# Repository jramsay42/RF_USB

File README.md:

# RF_USB
Simple pcb using a NRF2401 transceiver, inspired by Phil's lab

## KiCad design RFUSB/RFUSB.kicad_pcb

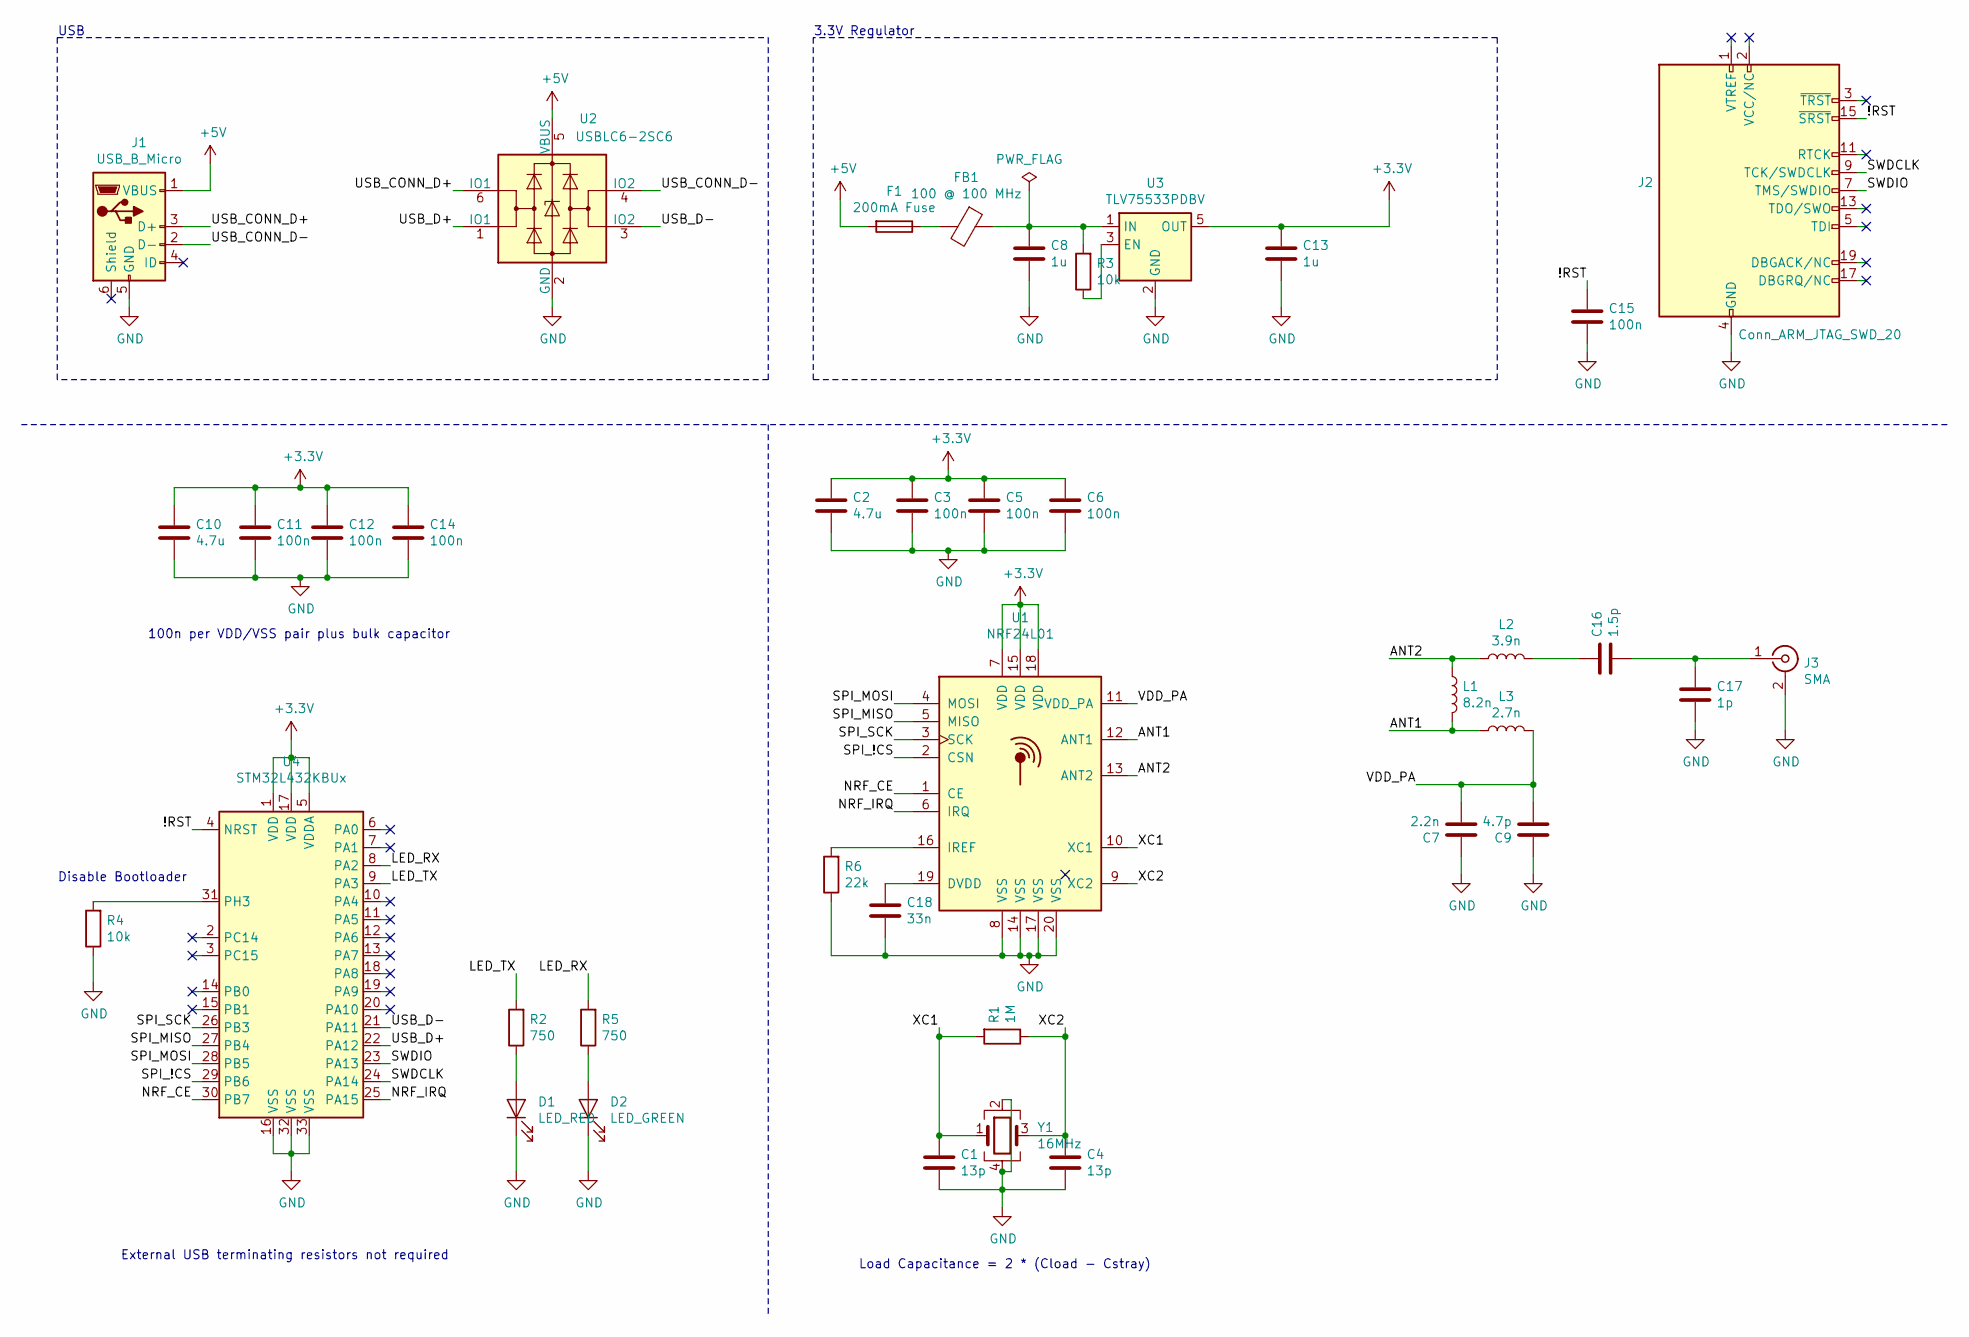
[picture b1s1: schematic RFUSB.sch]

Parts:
C1, C4: 13p; C_0402_1005Metric; MPN GJM1555C1H130GB01D
C2, C10: 4.7u; C_0402_1005Metric; MPN C1005X5R0J475M050BC
C3, C5, C6, C11, C12, C14, C15: 100n; C_0402_1005Metric; MPN 0402B104K160CT
C7: 2.2n; C_0402_1005Metric; MPN C0402C222K5RACTU
C8, C13: 1u; C_0402_1005Metric; MPN CL05A105KQ5NNNC
C9: 4.7p; C_0402_1005Metric; MPN CC0402CRNPO9BN4R7
C16: 1.5p; C_0402_1005Metric; MPN GRM1555C1H1R5CA01D
C17: 1p; C_0402_1005Metric; MPN GRM1555C1H1R0CA01D
C18: 33n; C_0402_1005Metric; MPN CL05A334KQ5NNNC
D1: LED_RED; D_0402_1005Metric; MPN APHHS1005SURCK
D2: LED_GREEN; D_0402_1005Metric; MPN APHHS1005CGCK
F1: 200mA Fuse; Fuse_0402_1005Metric; MPN F0402G0R20FNTR
FB1: 100 @ 100 MHz; L_0402_1005Metric; MPN 742792711
J1: USB_B_Micro; USB_Micro-B_Molex-105017-0001; MPN 1050170001
J2: Conn_ARM_JTAG_SWD_20; PinHeader_2x10_P2.54mm_Vertical_SMD; MPN 3020-20-0300-00
J3: SMA; SMA_Samtec_SMA-J-P-X-ST-EM1_EdgeMount; MPN SMA-J-P-H-ST-EM1
L1: 8.2n; L_0402_1005Metric; MPN L-07C8N2JV6T
L2: 3.9n; L_0402_1005Metric; MPN L-07C3N9SV6T
L3: 2.7n; L_0402_1005Metric; MPN L-07C2N7SV6T
R1: 1M; R_0402_1005Metric; MPN RC0402FR-071ML
R2, R5: 750; R_0402_1005Metric; MPN RC0402JR-07750RL
R3, R4: 10k; R_0402_1005Metric; MPN RC0402FR-0710KL
R6: 22k; R_0402_1005Metric; MPN RC0402FR-0722KL
U1: NRF24L01; QFN-20-1EP_4x4mm_P0.5mm_EP2.5x2.5mm; MPN NRF24L01
U2: USBLC6-2SC6; SOT-23-6; MPN USBLC6-2SC6
U3: TLV75533PDBV; SOT-23-5; MPN TLV75533PDBVR
U4: STM32L432KBUx; QFN-32-1EP_5x5mm_P0.5mm_EP3.45x3.45mm; MPN STM32L432KBU6
Y1: 16MHz; Crystal_SMD_3225-4Pin_3.2x2.5mm; MPN NX3225SA-16MHZ-STD-CSR-6

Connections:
+3V3: C2.1, C3.1, C5.1, C6.1, C10.1, C11.1, C12.1, C13.1, C14.1, U1.7 (VDD), U1.15 (VDD), U1.18 (VDD), U3.5 (OUT), U4.1 (VDD), U4.5 (VDDA), U4.17 (VDD)
+5V: F1.2, J1.1 (VBUS), U2.5 (VBUS)
/!RST: C15.1, J2.15 (~SRST~), U4.4 (NRST)
/ANT1: L1.2, L3.1, U1.12 (ANT1)
/ANT2: L1.1, L2.1, U1.13 (ANT2)
/LED_RX: R5.2, U4.8 (PA2)
/LED_TX: R2.2, U4.9 (PA3)
/NRF_CE: U1.1 (CE), U4.30 (PB7)
/NRF_IRQ: U1.6 (IRQ), U4.25 (PA15)
/SPI_!CS: U1.2 (CSN), U4.29 (PB6)
/SPI_MISO: U1.5 (MISO), U4.27 (PB4)
/SPI_MOSI: U1.4 (MOSI), U4.28 (PB5)
/SPI_SCK: U1.3 (SCK), U4.26 (PB3)
/SWDCLK: J2.9 (TCK/SWDCLK), U4.24 (PA14)
/SWDIO: J2.7 (TMS/SWDIO), U4.23 (PA13)
/USB_CONN_D+: J1.3 (D+), U2.6 (IO1)
/USB_CONN_D-: J1.2 (D-), U2.4 (IO2)
/USB_D+: U2.1 (IO1), U4.22 (PA12)
/USB_D-: U2.3 (IO2), U4.21 (PA11)
/VDD_PA: C7.2, C9.2, L3.2, U1.11 (VDD_PA)
/XC1: C1.1, R1.2, U1.10 (XC1), Y1.1
/XC2: C4.1, R1.1, U1.9 (XC2), Y1.3
GND: C1.2, C2.2, C3.2, C4.2, C5.2, C6.2, C7.1, C8.2, C9.1, C10.2, C11.2, C12.2, C13.2, C14.2, C15.2, C17.2, C18.2, D1.1 (K), D2.1 (K), J1.5 (GND), J2.4 (GND), J2.6 (GND), J2.8 (GND), J2.10 (GND), J2.12 (GND), J2.14 (GND), J2.16 (GND), J2.18 (GND), J2.20 (GND), J3.2 (Ext), R4.1, R6.1, U1.8 (VSS), U1.14 (VSS), U1.17 (VSS), U1.20 (VSS), U2.2 (GND), U3.2 (GND), U4.16 (VSS), U4.32 (VSS), U4.33 (VSS), Y1.2, Y1.4
unnamed: C8.1, FB1.1, R3.2, U3.1 (IN)
unnamed: C16.1, L2.2
unnamed: C16.2, C17.1, J3.1 (In)
unnamed: C18.1, U1.19 (DVDD)
unnamed: D1.2 (A), R2.1
unnamed: D2.2 (A), R5.1
unnamed: F1.1, FB1.2
unnamed: R3.1, U3.3 (EN)
unnamed: R4.2, U4.31 (PH3)
unnamed: R6.2, U1.16 (IREF)

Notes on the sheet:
USB
Load Capacitance = 2 * (Cload - Cstray)
Disable Bootloader
3.3V Regulator
External USB terminating resistors not required
100n per VDD/VSS pair plus bulk capacitor

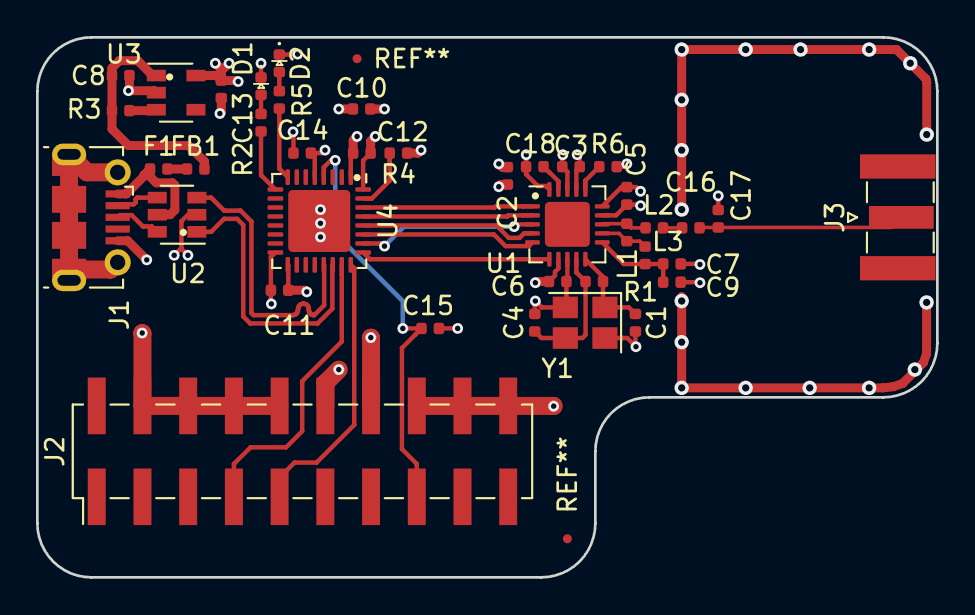
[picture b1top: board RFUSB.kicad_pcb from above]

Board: 4 copper layers, 50.0 x 30.0 mm, 39 parts (0 on the bottom side), 33 nets.

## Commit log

2021-04-07 Add files via upload
    First version, design files
